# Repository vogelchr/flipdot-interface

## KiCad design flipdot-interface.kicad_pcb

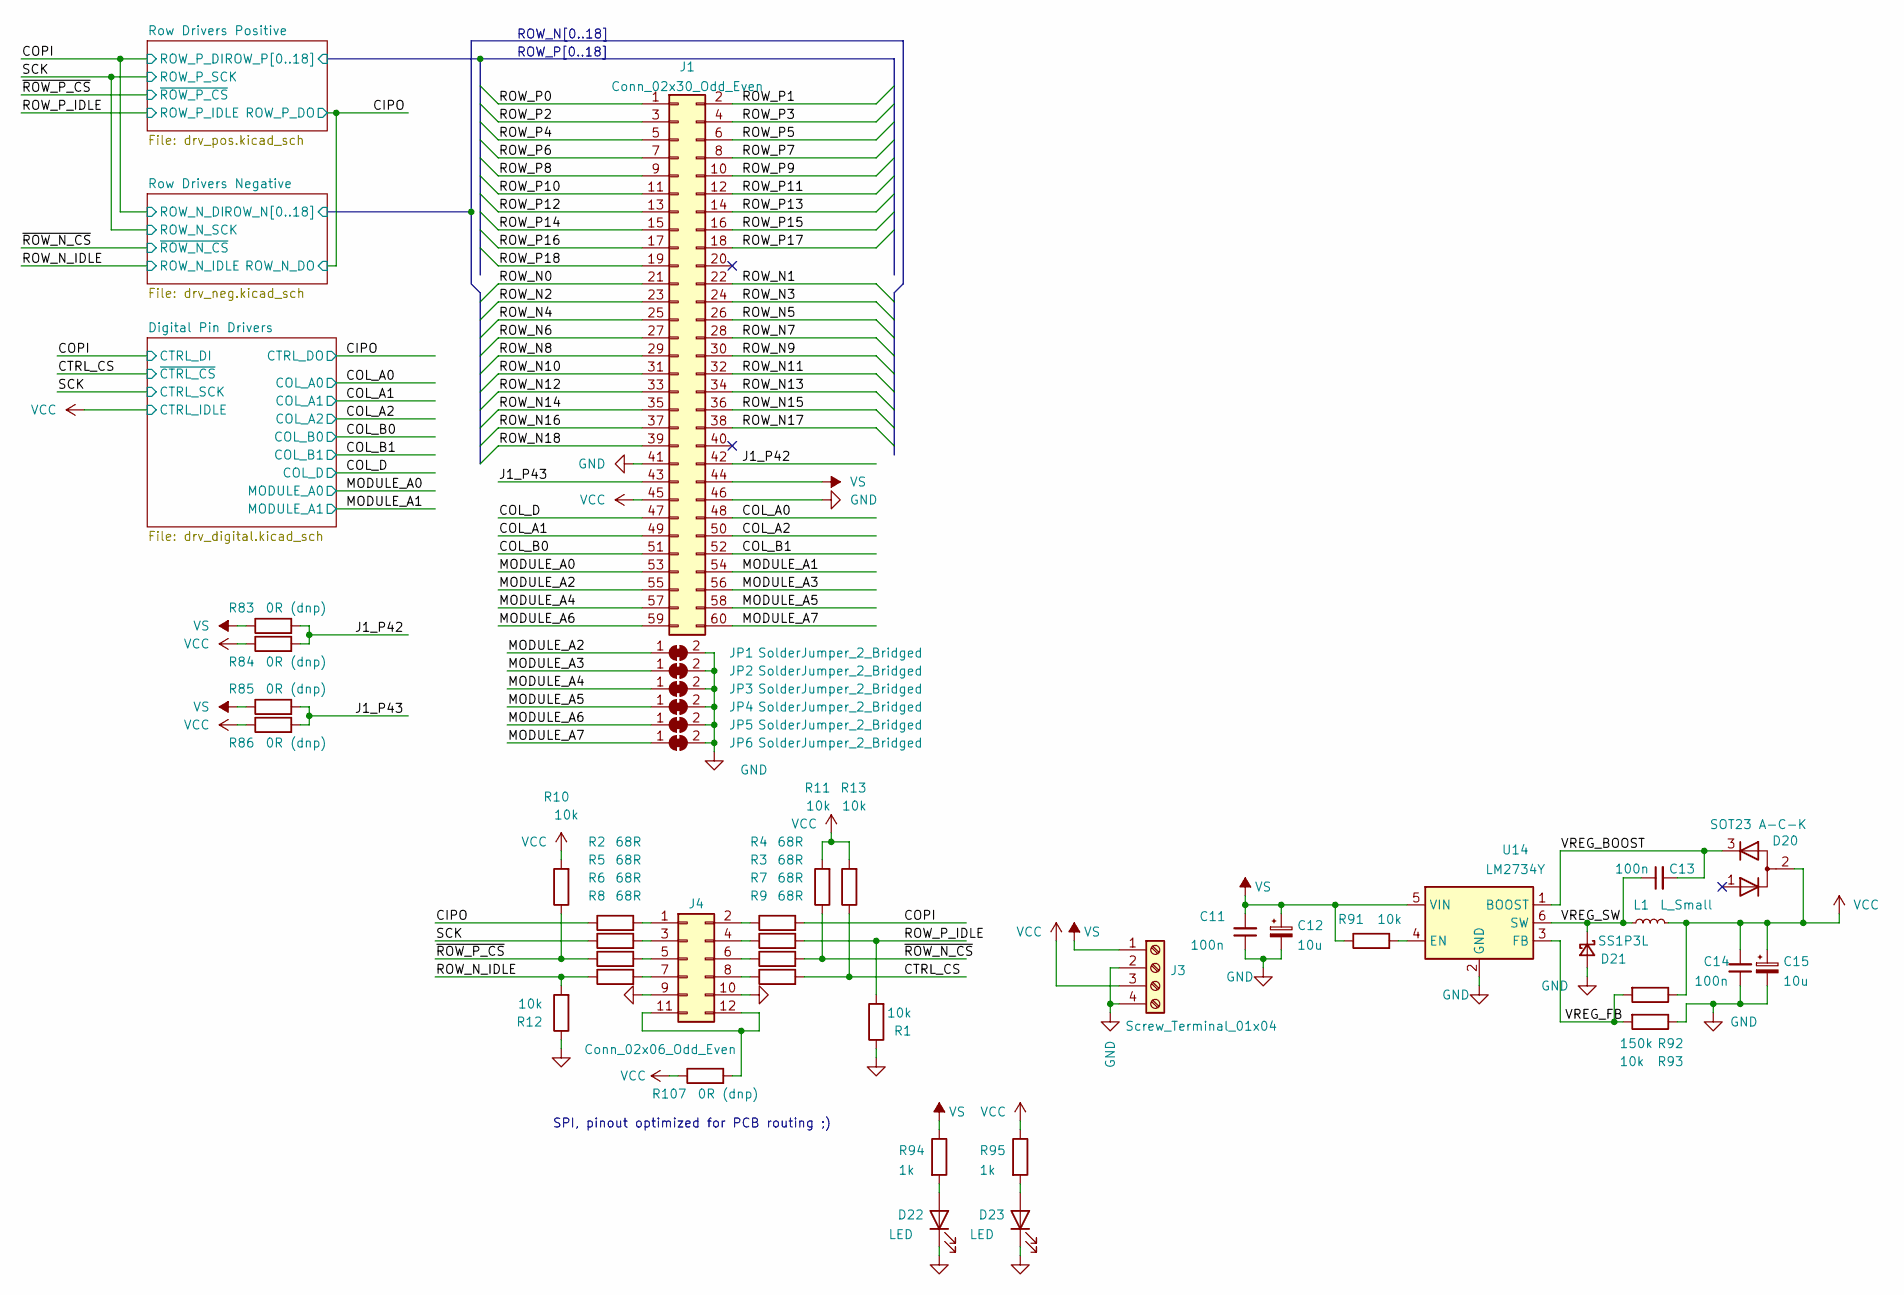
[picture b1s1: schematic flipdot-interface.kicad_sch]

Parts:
C11, C13, C14: 100n; C_0603_1608Metric
C12, C15: 10u; CP_EIA-3216-18_Kemet-A
D20: SOT23 A-C-K; SOT-23
D21: SS1P3L; D_SMF
D22, D23: LED; LED_0603_1608Metric
J1: Conn_02x30_Odd_Even; IDC-Header_2x30_P2.54mm_Vertical
J3: Screw_Terminal_01x04; TerminalBlock_MetzConnect_Type086_RT03404HBLC_1x04_P3.81mm_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
J4: Conn_02x06_Odd_Even; IDC-Header_2x06_P2.54mm_Vertical
JP1, JP2, JP3, JP4, JP5, JP6: SolderJumper_2_Bridged; SolderJumper-2_P1.3mm_Bridged_Pad1.0x1.5mm
L1: L_Small; L_Coilcraft_XxL4020
R1, R10, R11, R12, R13, R91, R93: 10k; R_0603_1608Metric
R2, R3, R4, R5, R6, R7, R8, R9: 68R; R_0603_1608Metric
R83, R84, R85, R86, R107: 0R (dnp); R_0603_1608Metric
R92: 150k; R_0603_1608Metric
R94, R95: 1k; R_0603_1608Metric
U14: LM2734Y; TSOT-23-6

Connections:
/CIPO: R2.1; also elsewhere on the board
/COL_A0: J1.48; also elsewhere on the board
/COL_A1: J1.49; also elsewhere on the board
/COL_A2: J1.50; also elsewhere on the board
/COL_B0: J1.51; also elsewhere on the board
/COL_B1: J1.52; also elsewhere on the board
/COL_D: J1.47; also elsewhere on the board
/COPI: R4.2; also elsewhere on the board
/CTRL_CS: R9.2, R13.1; also elsewhere on the board
/J1_P42: J1.42, R83.2, R84.2
/J1_P43: J1.43, R85.2, R86.2
/MODULE_A0: J1.53; also elsewhere on the board
/MODULE_A1: J1.54; also elsewhere on the board
/MODULE_A2: J1.55, JP1.1 (A)
/MODULE_A3: J1.56, JP2.1 (A)
/MODULE_A4: J1.57, JP3.1 (A)
/MODULE_A5: J1.58, JP4.1 (A)
/MODULE_A6: J1.59, JP5.1 (A)
/MODULE_A7: J1.60, JP6.1 (A)
/ROW_N_IDLE: R8.1, R12.2; also elsewhere on the board
/ROW_P_IDLE: R1.2, R3.2; also elsewhere on the board
/Row Drivers Negative/ROW_N0: J1.21; also elsewhere on the board
/Row Drivers Negative/ROW_N1: J1.22; also elsewhere on the board
/Row Drivers Negative/ROW_N2: J1.23; also elsewhere on the board
/Row Drivers Negative/ROW_N3: J1.24; also elsewhere on the board
/Row Drivers Negative/ROW_N4: J1.25; also elsewhere on the board
/Row Drivers Negative/ROW_N5: J1.26; also elsewhere on the board
/Row Drivers Negative/ROW_N6: J1.27; also elsewhere on the board
/Row Drivers Negative/ROW_N7: J1.28; also elsewhere on the board
/Row Drivers Negative/ROW_N8: J1.29; also elsewhere on the board
/Row Drivers Negative/ROW_N9: J1.30; also elsewhere on the board
/Row Drivers Negative/ROW_N10: J1.31; also elsewhere on the board
/Row Drivers Negative/ROW_N11: J1.32; also elsewhere on the board
/Row Drivers Negative/ROW_N12: J1.33; also elsewhere on the board
/Row Drivers Negative/ROW_N13: J1.34; also elsewhere on the board
/Row Drivers Negative/ROW_N14: J1.35; also elsewhere on the board
/Row Drivers Negative/ROW_N15: J1.36; also elsewhere on the board
/Row Drivers Negative/ROW_N16: J1.37; also elsewhere on the board
/Row Drivers Negative/ROW_N17: J1.38; also elsewhere on the board
/Row Drivers Negative/ROW_N18: J1.39; also elsewhere on the board
/Row Drivers Positive/ROW_P0: J1.1; also elsewhere on the board
/Row Drivers Positive/ROW_P1: J1.2; also elsewhere on the board
/Row Drivers Positive/ROW_P2: J1.3; also elsewhere on the board
/Row Drivers Positive/ROW_P3: J1.4; also elsewhere on the board
/Row Drivers Positive/ROW_P4: J1.5; also elsewhere on the board
/Row Drivers Positive/ROW_P5: J1.6; also elsewhere on the board
/Row Drivers Positive/ROW_P6: J1.7; also elsewhere on the board
/Row Drivers Positive/ROW_P7: J1.8; also elsewhere on the board
/Row Drivers Positive/ROW_P8: J1.9; also elsewhere on the board
/Row Drivers Positive/ROW_P9: J1.10; also elsewhere on the board
/Row Drivers Positive/ROW_P10: J1.11; also elsewhere on the board
/Row Drivers Positive/ROW_P11: J1.12; also elsewhere on the board
/Row Drivers Positive/ROW_P12: J1.13; also elsewhere on the board
/Row Drivers Positive/ROW_P13: J1.14; also elsewhere on the board
/Row Drivers Positive/ROW_P14: J1.15; also elsewhere on the board
/Row Drivers Positive/ROW_P15: J1.16; also elsewhere on the board
/Row Drivers Positive/ROW_P16: J1.17; also elsewhere on the board
/Row Drivers Positive/ROW_P17: J1.18; also elsewhere on the board
/Row Drivers Positive/ROW_P18: J1.19; also elsewhere on the board
/SCK: R5.1; also elsewhere on the board
/VREG_BOOST: C13.2, D20.3 (K), U14.1 (BOOST)
/VREG_FB: R92.2, R93.2, U14.3 (FB)
/VREG_SW: C13.1, D21.1 (K), L1.1, U14.6 (SW)
/~ROW_N_CS: R7.2, R11.1; also elsewhere on the board
/~ROW_P_CS: R6.1, R10.1; also elsewhere on the board
GND: C11.1, C12.2, C14.1, C15.2, D21.2 (A), D22.1 (K), D23.1 (K), J1.41, J1.46, J3.2, J3.4, J4.9, J4.10, JP1.2 (B), JP2.2 (B), JP3.2 (B), JP4.2 (B), JP5.2 (B), JP6.2 (B), R1.1, R12.1, R93.1, U14.2 (GND); also elsewhere on the board
unnamed: D22.2 (A), R94.2
unnamed: D23.2 (A), R95.2
unnamed: J4.1, R2.2
unnamed: J4.2, R4.1
unnamed: J4.3, R5.2
unnamed: J4.4, R3.1
unnamed: J4.5, R6.2
unnamed: J4.6, R7.1
unnamed: J4.7, R8.2
unnamed: J4.8, R9.1
unnamed: J4.11, J4.12, R107.2
unnamed: R91.2, U14.4 (EN)
VCC: C14.2, C15.1, D20.2 (A), J1.45, J3.3, L1.2, R10.2, R11.2, R13.2, R84.1, R86.1, R92.1, R95.1, R107.1; also elsewhere on the board
VS: C11.2, C12.1, J1.44, J3.1, R83.1, R85.1, R91.1, R94.1, U14.5 (VIN); also elsewhere on the board

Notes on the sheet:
ROW_N[0..18]
ROW_P[0..18]
SPI, pinout optimized for PCB routing ;)

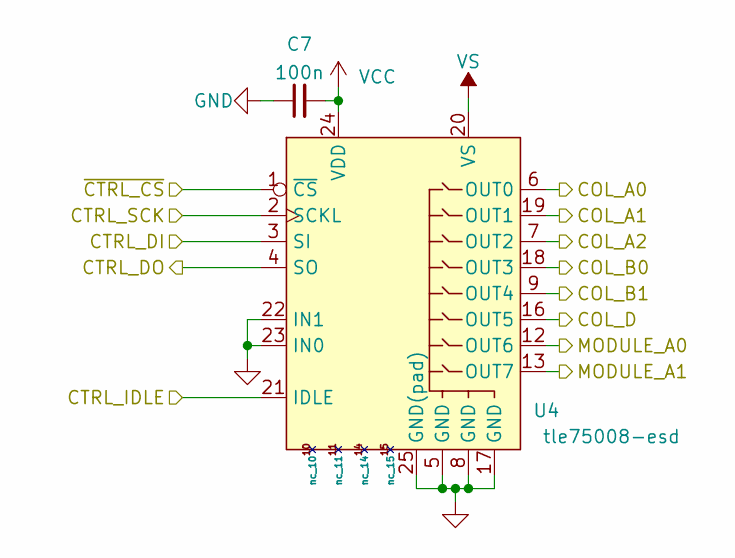
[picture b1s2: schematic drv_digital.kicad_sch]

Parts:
C7: 100n; C_0603_1608Metric
U4: tle75008-esd; Infineon-PG-TSDSO-24-51

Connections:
/CIPO: U4.4 (SO); also elsewhere on the board
/COL_A0: U4.6 (OUT0); also elsewhere on the board
/COL_A1: U4.19 (OUT1); also elsewhere on the board
/COL_A2: U4.7 (OUT2); also elsewhere on the board
/COL_B0: U4.18 (OUT3); also elsewhere on the board
/COL_B1: U4.9 (OUT4); also elsewhere on the board
/COL_D: U4.16 (OUT5); also elsewhere on the board
/COPI: U4.3 (SI); also elsewhere on the board
/CTRL_CS: U4.1 (~CS); also elsewhere on the board
/MODULE_A0: U4.12 (OUT6); also elsewhere on the board
/MODULE_A1: U4.13 (OUT7); also elsewhere on the board
/SCK: U4.2 (SCKL); also elsewhere on the board
GND: C7.1, U4.5 (GND), U4.8 (GND), U4.17 (GND), U4.22 (IN1), U4.23 (IN0), U4.25 (GND(pad)); also elsewhere on the board
VCC: C7.2, U4.21 (IDLE), U4.24 (VDD); also elsewhere on the board
VS: U4.20 (VS); also elsewhere on the board

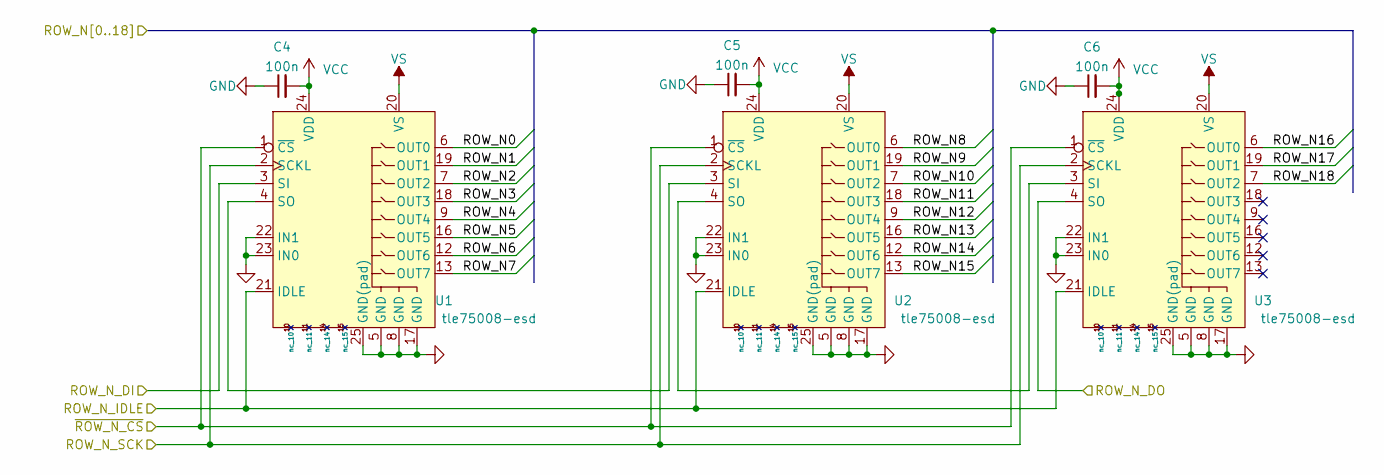
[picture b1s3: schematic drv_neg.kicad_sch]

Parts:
C4, C5, C6: 100n; C_0603_1608Metric
U1, U2, U3: tle75008-esd; Infineon-PG-TSDSO-24-51

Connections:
/CIPO: U3.4 (SO); also elsewhere on the board
/COPI: U1.3 (SI); also elsewhere on the board
/ROW_N_IDLE: U1.21 (IDLE), U2.21 (IDLE), U3.21 (IDLE); also elsewhere on the board
/Row Drivers Negative/ROW_N0: U1.6 (OUT0); also elsewhere on the board
/Row Drivers Negative/ROW_N1: U1.19 (OUT1); also elsewhere on the board
/Row Drivers Negative/ROW_N2: U1.7 (OUT2); also elsewhere on the board
/Row Drivers Negative/ROW_N3: U1.18 (OUT3); also elsewhere on the board
/Row Drivers Negative/ROW_N4: U1.9 (OUT4); also elsewhere on the board
/Row Drivers Negative/ROW_N5: U1.16 (OUT5); also elsewhere on the board
/Row Drivers Negative/ROW_N6: U1.12 (OUT6); also elsewhere on the board
/Row Drivers Negative/ROW_N7: U1.13 (OUT7); also elsewhere on the board
/Row Drivers Negative/ROW_N8: U2.6 (OUT0); also elsewhere on the board
/Row Drivers Negative/ROW_N9: U2.19 (OUT1); also elsewhere on the board
/Row Drivers Negative/ROW_N10: U2.7 (OUT2); also elsewhere on the board
/Row Drivers Negative/ROW_N11: U2.18 (OUT3); also elsewhere on the board
/Row Drivers Negative/ROW_N12: U2.9 (OUT4); also elsewhere on the board
/Row Drivers Negative/ROW_N13: U2.16 (OUT5); also elsewhere on the board
/Row Drivers Negative/ROW_N14: U2.12 (OUT6); also elsewhere on the board
/Row Drivers Negative/ROW_N15: U2.13 (OUT7); also elsewhere on the board
/Row Drivers Negative/ROW_N16: U3.6 (OUT0); also elsewhere on the board
/Row Drivers Negative/ROW_N17: U3.19 (OUT1); also elsewhere on the board
/Row Drivers Negative/ROW_N18: U3.7 (OUT2); also elsewhere on the board
/SCK: U1.2 (SCKL), U2.2 (SCKL), U3.2 (SCKL); also elsewhere on the board
/~ROW_N_CS: U1.1 (~CS), U2.1 (~CS), U3.1 (~CS); also elsewhere on the board
GND: C4.1, C5.1, C6.1, U1.5 (GND), U1.8 (GND), U1.17 (GND), U1.22 (IN1), U1.23 (IN0), U1.25 (GND(pad)), U2.5 (GND), U2.8 (GND), U2.17 (GND), U2.22 (IN1), U2.23 (IN0), U2.25 (GND(pad)), U3.5 (GND), U3.8 (GND), U3.17 (GND), U3.22 (IN1), U3.23 (IN0), U3.25 (GND(pad)); also elsewhere on the board
unnamed: U1.4 (SO), U2.3 (SI)
unnamed: U2.4 (SO), U3.3 (SI)
VCC: C4.2, C5.2, C6.2, U1.24 (VDD), U2.24 (VDD), U3.24 (VDD); also elsewhere on the board
VS: U1.20 (VS), U2.20 (VS), U3.20 (VS); also elsewhere on the board

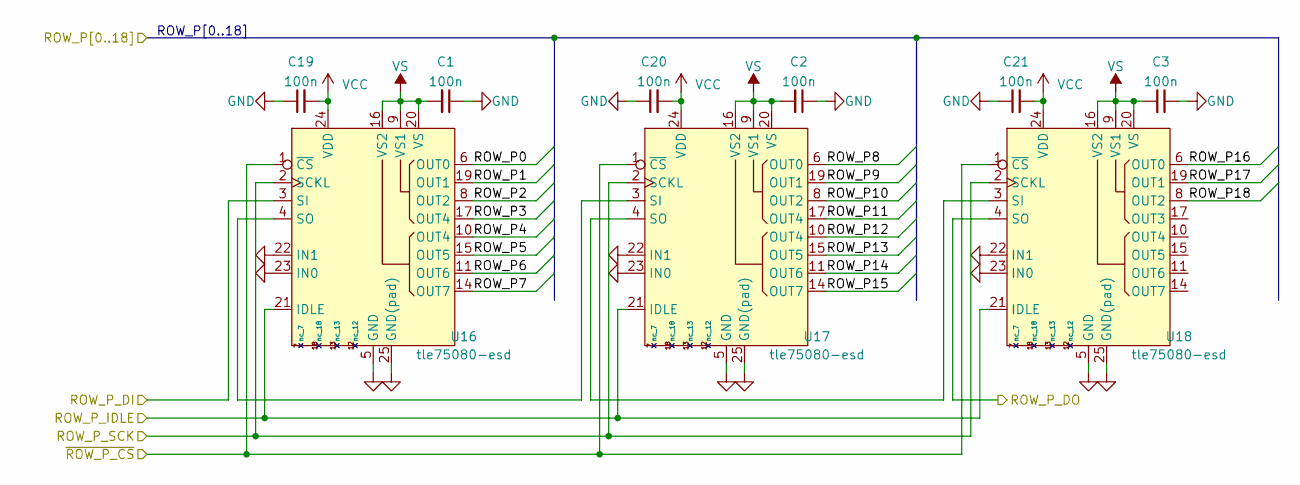
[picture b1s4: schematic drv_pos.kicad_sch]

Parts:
C1, C2, C3, C19, C20, C21: 100n; C_0603_1608Metric
U16, U17, U18: tle75080-esd; Infineon-PG-TSDSO-24-51

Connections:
/CIPO: U18.4 (SO); also elsewhere on the board
/COPI: U16.3 (SI); also elsewhere on the board
/ROW_P_IDLE: U16.21 (IDLE), U17.21 (IDLE), U18.21 (IDLE); also elsewhere on the board
/Row Drivers Positive/ROW_P0: U16.6 (OUT0); also elsewhere on the board
/Row Drivers Positive/ROW_P1: U16.19 (OUT1); also elsewhere on the board
/Row Drivers Positive/ROW_P2: U16.8 (OUT2); also elsewhere on the board
/Row Drivers Positive/ROW_P3: U16.17 (OUT4); also elsewhere on the board
/Row Drivers Positive/ROW_P4: U16.10 (OUT4); also elsewhere on the board
/Row Drivers Positive/ROW_P5: U16.15 (OUT5); also elsewhere on the board
/Row Drivers Positive/ROW_P6: U16.11 (OUT6); also elsewhere on the board
/Row Drivers Positive/ROW_P7: U16.14 (OUT7); also elsewhere on the board
/Row Drivers Positive/ROW_P8: U17.6 (OUT0); also elsewhere on the board
/Row Drivers Positive/ROW_P9: U17.19 (OUT1); also elsewhere on the board
/Row Drivers Positive/ROW_P10: U17.8 (OUT2); also elsewhere on the board
/Row Drivers Positive/ROW_P11: U17.17 (OUT4); also elsewhere on the board
/Row Drivers Positive/ROW_P12: U17.10 (OUT4); also elsewhere on the board
/Row Drivers Positive/ROW_P13: U17.15 (OUT5); also elsewhere on the board
/Row Drivers Positive/ROW_P14: U17.11 (OUT6); also elsewhere on the board
/Row Drivers Positive/ROW_P15: U17.14 (OUT7); also elsewhere on the board
/Row Drivers Positive/ROW_P16: U18.6 (OUT0); also elsewhere on the board
/Row Drivers Positive/ROW_P17: U18.19 (OUT1); also elsewhere on the board
/Row Drivers Positive/ROW_P18: U18.8 (OUT2); also elsewhere on the board
/SCK: U16.2 (SCKL), U17.2 (SCKL), U18.2 (SCKL); also elsewhere on the board
/~ROW_P_CS: U16.1 (~CS), U17.1 (~CS), U18.1 (~CS); also elsewhere on the board
GND: C1.1, C2.1, C3.1, C19.1, C20.1, C21.1, U16.5 (GND), U16.22 (IN1), U16.23 (IN0), U16.25 (GND(pad)), U17.5 (GND), U17.22 (IN1), U17.23 (IN0), U17.25 (GND(pad)), U18.5 (GND), U18.22 (IN1), U18.23 (IN0), U18.25 (GND(pad)); also elsewhere on the board
unnamed: U16.4 (SO), U17.3 (SI)
unnamed: U17.4 (SO), U18.3 (SI)
VCC: C19.2, C20.2, C21.2, U16.24 (VDD), U17.24 (VDD), U18.24 (VDD); also elsewhere on the board
VS: C1.2, C2.2, C3.2, U16.9 (VS1), U16.16 (VS2), U16.20 (VS), U17.9 (VS1), U17.16 (VS2), U17.20 (VS), U18.9 (VS1), U18.16 (VS2), U18.20 (VS); also elsewhere on the board

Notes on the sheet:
ROW_P[0..18]

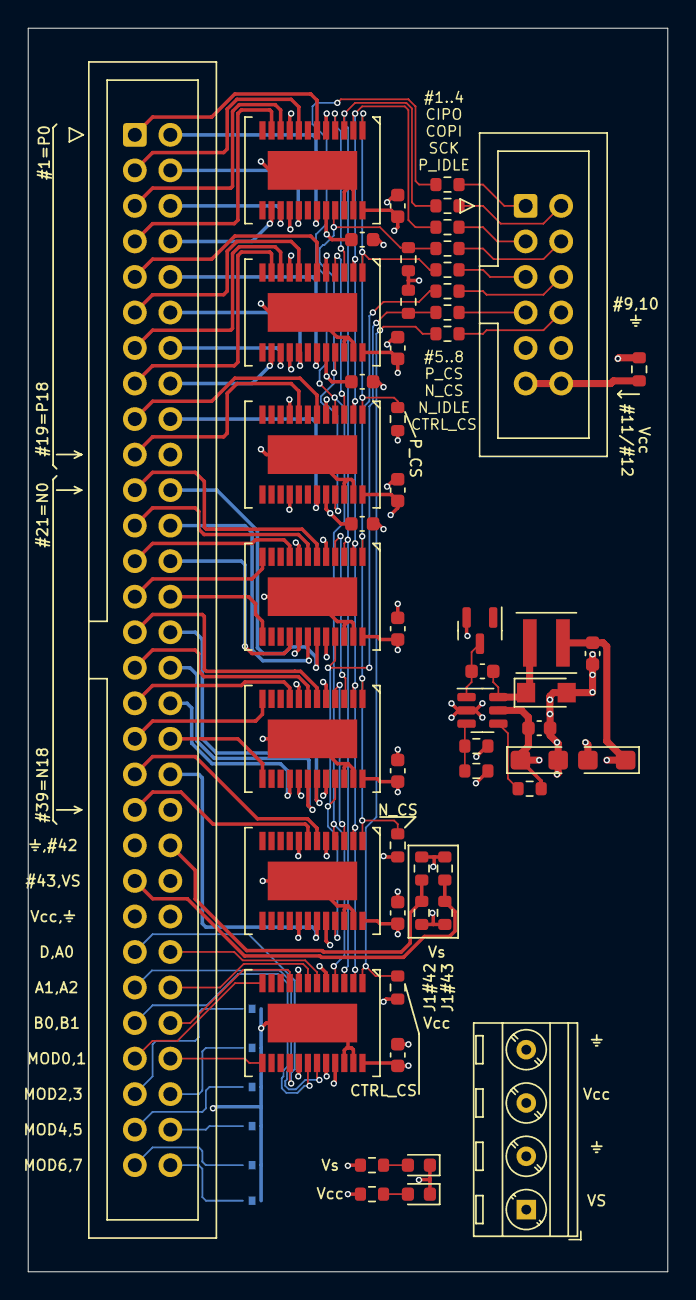
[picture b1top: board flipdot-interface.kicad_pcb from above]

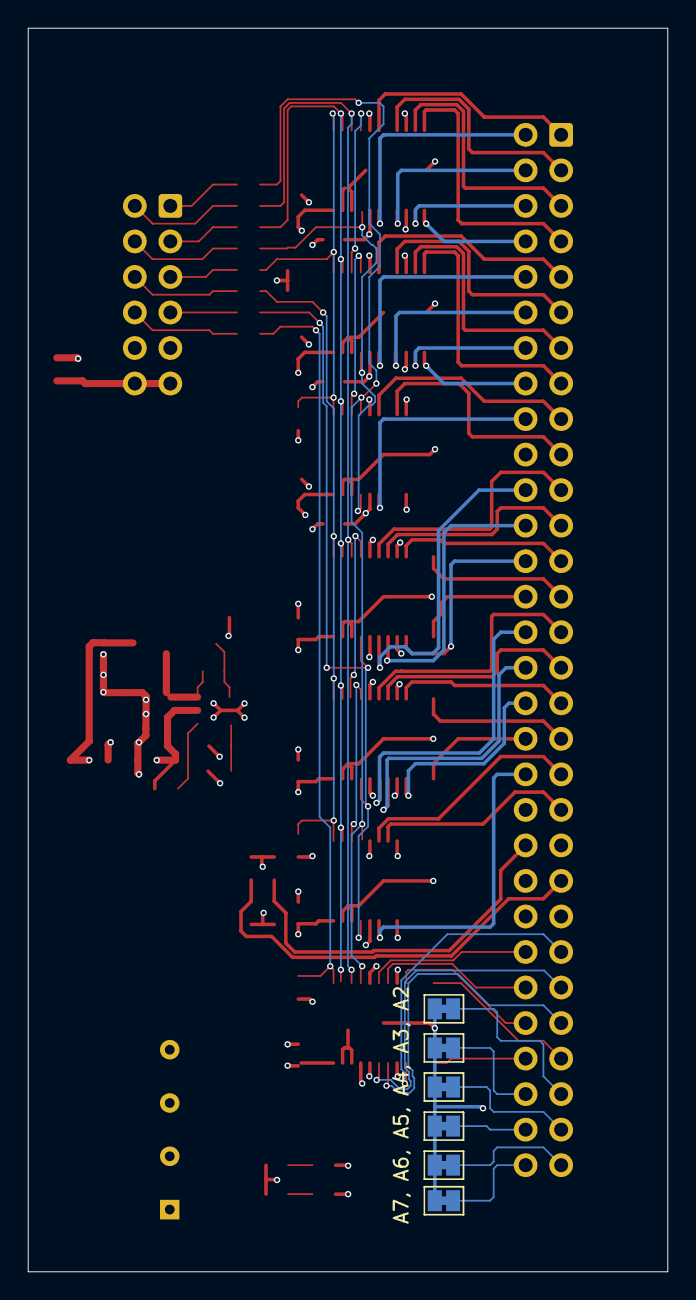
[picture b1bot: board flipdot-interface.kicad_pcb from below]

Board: 4 copper layers, 45.7 x 88.9 mm, 60 parts (6 on the bottom side), 84 nets.

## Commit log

2021-10-23 initially empty repository
2021-10-23 first checkin
2021-10-23 pdfs of first attempt
2021-10-24 moar woerk...
2021-11-03 moak woerk
2021-11-03 moar woerk
2021-11-03 Fabrication and PDFs for 20211103.
2021-11-04 add fabrication files
2021-11-05 more work
2021-11-20 More work, moved digital stuff to sub-schematic.
2021-11-20 Added pdf schematic for previous version.
2021-11-20 add #auto_saved_files# to gitignore
2021-11-20 Change positive drivers to a TLE75080-ESD, octal high side driver
2021-11-21 Change negative drivers to a TLE75008-ESD, octal low side driver.
